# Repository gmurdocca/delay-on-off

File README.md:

## What does it do?

This circuit was designed to add power-on-after-AC-resume support to a device that needs someone to press a momentary-action push button to turn the device on.

This repo contains KiCad design files for building a monostable multivibrator high-low pulse circuit that provides delayed on-off momentary action switch actuation.

## Why?

Any device that doesn't support power-on-after-AC-resume will stay off if AC is temporarily lost. This is bad if you need the device to be powered on as often as possible. This circuit solves this problem by implementing an electronic switch that presses the power button automatically.

## Requirements and installation

Open the files in KiCad, create gerber files and a drill file and send them to a fabricator (eg. http://dirtypcbs.com/)

This circuit will auto-power-on devices when AC is restored if:

* the device has a simple 2-pin connector behind a momentary action power button that, when shorted, will power the device on
* has a 5-12 volt DC rail that is permanently up when AC is restored (this is used to power the circuit and start the timer)
* the device's power button needs to be pressed and released a short time after AC power is restored

## Typical Installation

* If the device is powered by a standard ATX PSU:
  * connect the +5v stand-by terminal (purple lead) on the PSU to the positive power-in header
  * connect any ground terminal (any black lead) on the PSU to the negative power-in header
  * connect the positive side of your device's push-button contact to the positive side of the output header
  * connect the negative side of your device's push-button contact to the negative side ot the output header

## Config

Stock components as shown on the schematic will cause the circuit to "press" the power button on the target device ~2 seconds after AC resume, and "release" the power button ~1 second after that. The power button will stay "released" permanently until the next AC power cycle.

The target device's power button will function as normal. After automatic power on, this circuit will remain dormant until AC is cycled.

Changing the values of C1 wnd C2 will adjust the time before power button is pressed and the duration of the press respectively (higher capacitance = longer delays). These values should be changed as per standard 555 timer monostable multivibrator circuits which are well documented.

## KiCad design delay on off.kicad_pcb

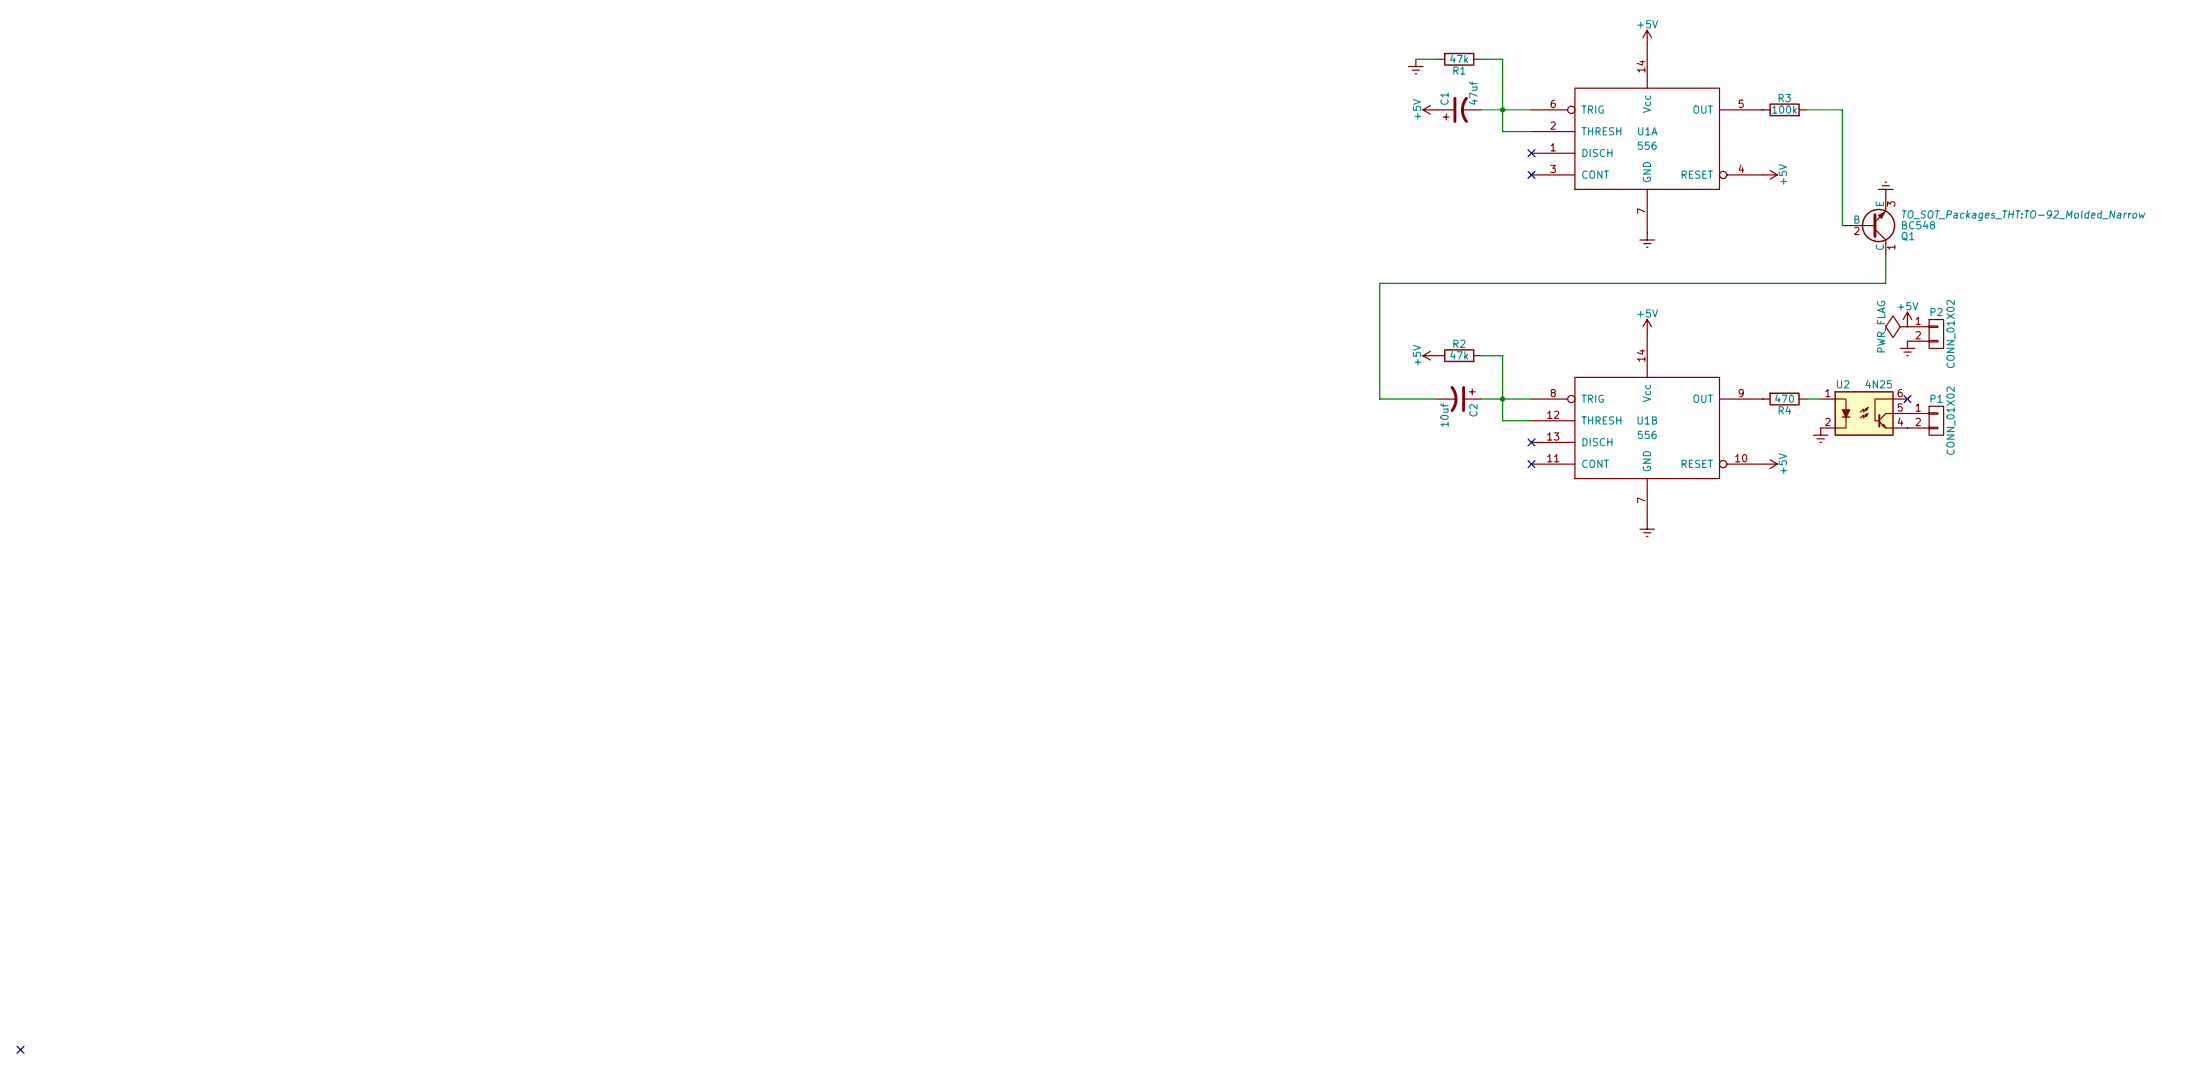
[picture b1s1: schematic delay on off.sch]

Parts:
C1: 47uf; C_Radial_D6.3_L11.2_P2.5
C2: 10uf; C_Radial_D5_L11_P2.5
P1, P2: CONN_01X02; Pin_Header_Straight_1x02
Q1: BC548; TO-92_Molded_Narrow
R1, R2: 47k; Resistor_Horizontal_RM10mm
R3: 100k; Resistor_Horizontal_RM10mm
R4: 470; Resistor_Horizontal_RM10mm
U1: 556; DIP-14_W7.62mm
U2: 4N25; Optocoupler_6pin_wide_Stile-II

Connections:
+5V: C1.1, P2.1, R2.1, U1.4 (RESET), U1.10 (RESET), U1.14 (Vcc)
Earth: P2.2, Q1.3 (E), R1.2, U1.7 (GND), U2.2
unnamed: C1.2, R1.1, U1.2 (THRESH), U1.6 (TRIG)
unnamed: C2.1, R2.2, U1.8 (TRIG), U1.12 (THRESH)
unnamed: C2.2, Q1.1 (C)
unnamed: P1.1, U2.5
unnamed: P1.2, U2.4
unnamed: Q1.2 (B), R3.2
unnamed: R3.1, U1.5 (OUT)
unnamed: R4.1, U2.1
unnamed: R4.2, U1.9 (OUT)

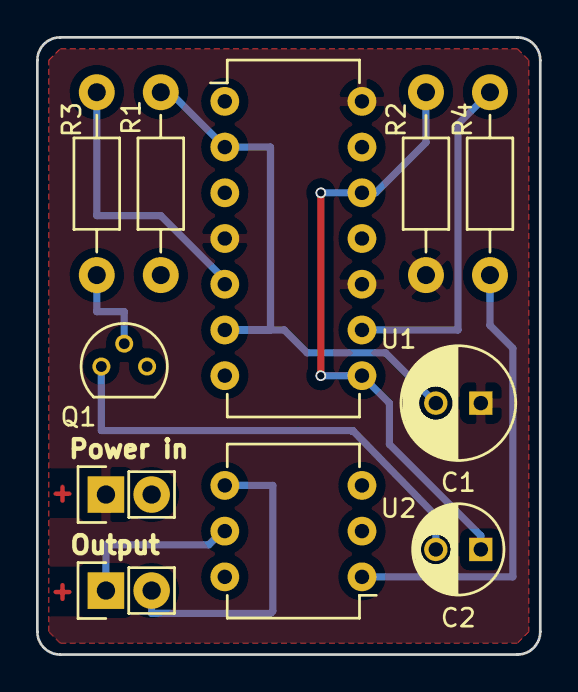
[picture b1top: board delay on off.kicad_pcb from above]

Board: 2 copper layers, 27.9 x 34.3 mm, 11 parts (0 on the bottom side), 11 nets.

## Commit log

2016-11-27 Adding KiCad project files
2016-11-27 add README
2016-11-27 add fabricator info
2016-11-27 add pic to readme
2016-11-27 edit readme
2016-11-28 fix readme
2016-11-28 typo
2016-11-28 clarify config
